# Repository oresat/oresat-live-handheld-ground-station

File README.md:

# Introduction
The OreSat Live Handheld Ground Station (HGS) project provides everything you need to build your own ground station capable of receiving images transmitted from OreSat in Low Earth Orbit.  HGS is designed to be inexpensive, easy to assemble, and simple to use so that it can be built by Middle and High School students.  The entire design is open source to encourage reuse and experimentation.

HGS is a portable unit built around a high gain directional antenna. Using a mobile phone application to locate OreSat, you aim the antenna to get the best possible signal. The live images are then received by the groundstation, error corrections are applied and the image is made available to any WiFi capable device through a built-in web page.

OreSat HGS act as a wifi access point providing an unsecured wireless network named "OreSatLive".  Devices identify the network as a hotspot requiring the user to sign-in for Internet access.  To view the image stream simply:
1. Connect your wifi to the "OreSatLive" network
2. Choose to sign-in when prompted
3. The OreSat Live web interface will open automatically

HGS was created for use with the OreSat mission, but it is designed to be used by any group interested in long range image transmission.  The handheld ground stations can be reused for other cubesat or balloon launches.

Once the final design is completed, users will be able to purchase all of the required parts as a kit from https://www.crowdsupply.com/

# HGS Parts List
All of the required parts to build HGS can be found in the Bill of Materials [(BOM)](BOM.md)

# Hardware Setup
Build your Handheld Ground Station kit according to the [Assembly Instructions](hgs-model/assembly-instructions/OreSat_Live_HGS_Assembly.pdf)

# Software Setup
1. [Download the SD card image oresat_hgs_14_jun_2019.img](https://drive.google.com/a/pdx.edu/uc?id=1BvP8ltkEwoBRSbCfQXceEiuxpVhkSf37&export=download)
2. Write the SD card image to a 2GB or larger card.  The [Raspberry Pi documentation](https://www.raspberrypi.org/documentation/installation/installing-images/) explains the procedure.

# Startup Procedure
1. Install the SD card in Raspberry Pi
2. Insert phone into the holder
3. Connect Raspberry Pi power cable to the USB power bank
4. Load Satellite AR app on phone and select OreSat
5. Point the ground station in the direction of OreSat
3. Connect your viewing devices to the "OreSatLive" wifi network

# Design Details
## Software Design
If you would like to build the software system from source follow the [Build Instructions](software/BUILD.md)

## Mechanical Design
You can 3D print all of the [mechanical parts](hgs-model/README.md)  

## Circuit Board Design
The integrated antenna backplane and matching network [circuit board design files](backplane/README.md)

# Related Projects
[OreSat Live](https://github.com/oresat/oresat-dxwifi-software) for software and firmware used on OreSat satellite

[Mini OreSat](https://github.com/oresat/oresat-live-mini-oresat) combines the OreSat Live software with a Raspberry Pi Zero W + Pi Camera to create platform for hobbyist and classroom experiments with high-altitude ballooning.

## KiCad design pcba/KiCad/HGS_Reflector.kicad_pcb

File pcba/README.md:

# Backplane for Handheld Ground Station
Schematic files for the backplane, including impedence matching circuit for connecting the antenna to the rest of the components.

Schematic files created using KiCad 5.1.2.
- **.pro** to open up Kicad project
- **.kicad_pcb** for the PCB layout
- **.kicad_mod** for the individual footprints

## Microstrip Dimensions
Backplane material: FR-4 PCB material, 0.5 oz copper, 1.58 mm thick, Er 4.34 @ 1 GHz
Note: Do not remove any of the copper ground plane on the other side of the board beneath the traces.  

Microstrip widths for various impedances:
```
50 ohm
	Width:  3.05184 mm
	Length: Arbitrary

83 ohm?
	Width: 1.20938 mm
	Length: Arbitrary

140 ohm
	Width:  0.238155 mm
	Length: Arbitrary
```

## 1/4 Wave Matching Transformer Design:
	Start at connector
	Arbitrary length of 50 ohm
	Lambda/4 length (17.7623 mm) of 83.66 ohm
	Arbitrary length of 140 ohm
	End at the helix element

## Other notes
[Source for Raspberry Pi Zero footprint dimensions](http://www.electronics-lab.com/raspberry-pi-zero-footprint-and-dimensions/)\
[Source for wf-np9202 footprint dimensions](https://www.aliexpress.com/item/wireless-net-card-LAN-NIC-module-AR9271-150M-wireless-LAN-net-card-industrial-module/32746090657.html?tt=sns_none&aff_platform=default&cpt=1557507604073&sk=cC0ydLx2&aff_trace_key=5d988d9ac55b4f4d80da408161a19463-1557507604073-02869-cC0ydLx2&terminal_id=523d634d52754e72ad5634ec5f8829c2)

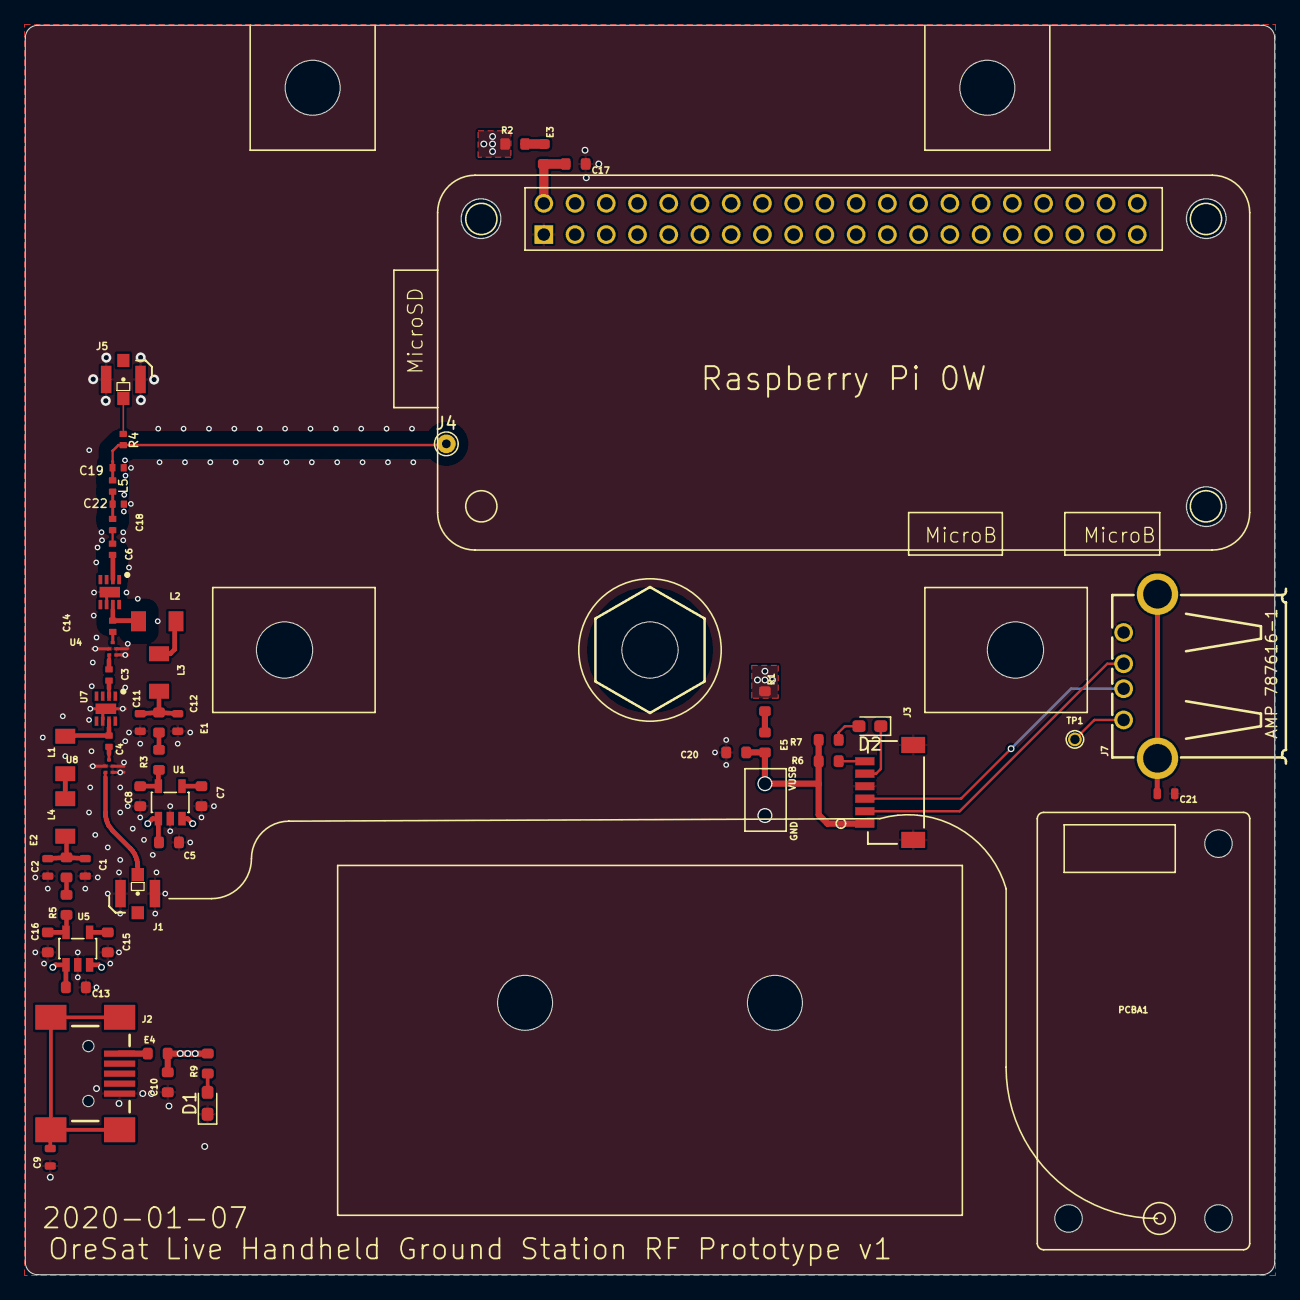
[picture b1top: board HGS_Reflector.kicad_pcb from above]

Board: 4 copper layers, 100.0 x 100.0 mm, 64 parts (0 on the bottom side), 38 nets.

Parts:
@HOLE0, @HOLE1, @HOLE2, @HOLE3, @HOLE4, @HOLE5, @HOLE6: (no value)
C1, C9, C11, C21: 100 pF; 0603-C-NOSILK
C2, C12: 1 uF; 0603-C-NOSILK
C3, C4, C6, C14, C18: 100 pF; 0402-C-NOSILK
C5, C10, C13, C17, C20: 1 uF; 0603-B-NOSILK
C7, C15: 10 nF; 0603-B-NOSILK
C8, C16: 2.2 uF; 0603-B-NOSILK
C19: 0.9 pF; 0402-C-NOSILK
C22: 1.0 pF; 0402-C-NOSILK
D1, D2: Green; LED_0603_1608Metric_Pad1.05x0.95mm_HandSolder
E1, E2, E5: BLM18GG471SZ1D; 0603-B-NOSILK
E3, E4: BLM18DN381SZ1D; 0603-B-NOSILK
J1: U.FL
J2: USB_C_Plug_USB2.0; USB-MINIB
J3: SM06B-SRSS-TB(LF)(SN); CONN_SM06B-SRSS-TB_JST
J4: Conn_01x01_Pin; TestPoint_THTPad_D1.5mm_Drill0.7mm
J5: 132134-10; U.FL
J7: USB_HOST_W/CHASSIS_GND; GHI2_USB_HOST_HORIZONTAL_W_CHASSIS_GND
L1, L2: 10n; L3216C
L3, L4: 8n; L3216C
L5: 4.3 nH; 0402-C-NOSILK
PCBA1: WF-NP9202WF; WF-NP9202
PCBA2: RASP_PI_0WPI_0W; RASP_PI_0W
R1, R2, R3, R5, R6: 0; 0603-B-NOSILK
R4: R_Small_US; 0402-C-NOSILK
R7, R9: 1k; 0603-B-NOSILK
TP1: Test-Point; TestPoint-0.75mm-th
U1, U5: LP2985-N; SOT-23 LP2985
U2, U7: TQP3M9037
U4: QPQ1907
U8: B39162B9417K610; QPQ1907

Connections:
/RF1: C19.2, J4.1, L5.1, R4.2
/RF2: C18.2, C22.1, L5.2
/RF3: C6.2, U2.2 (RF_IN)
/RF4: C14.1, L2.1, U2.7 (RF_OUT)
GND: C1.2, C2.2, C5.1, C7.2, C8.2, C9.1, C10.1, C11.2, C12.2, C13.1, C15.2, C16.2, C17.1, C19.1, C20.1, C21.1, C22.2, D1.1 (K), J1.1 (GND@0), J1.2 (GND@1), J2.A1 (GND), J3.4, J3.7, J3.8 (7), J5.1 (GND@0), J5.2 (GND@1), J7.4 (GND), PCBA2.GND, U1.2 (GND), U2.6 (SHUT_DOWN), U2.9 (GND), U4.2 (GND), U4.3 (GND), U4.5 (GND), U5.2 (GND), U7.6 (SHUT_DOWN), U7.9 (GND), U8.2 (GND), U8.3 (GND), U8.5 (GND)
unnamed: C1.1, C2.1, E2.2, L4.2
unnamed: C11.1, C12.1, E1.2, L3.2
unnamed: C17.2, E3.2, PCBA2.5V
unnamed: C6.1, C18.1
unnamed: C20.2, E5.2, J3.1, R6.1, R7.2
unnamed: D1.2 (A), R9.1
unnamed: D2.2 (A), R7.1
unnamed: D2.1 (K), J3.5
unnamed: E1.1, R3.2
unnamed: E2.1, R5.2
unnamed: E3.1, R2.2
unnamed: E4.1, J2.A4 (VBUS)
unnamed: E5.1, R1.2
unnamed: J1.FEED (SIGNAL), U8.4 (OUT)
unnamed: C9.2, J2.S1 (SHIELD)
unnamed: J3.6, R6.2
unnamed: J5.FEED (SIGNAL), R4.1
unnamed: C21.2, J7.5 (CG1), J7.6 (CG2)
unnamed: J3.2, J7.3 (D+)
unnamed: J3.3, J7.2 (D-)
unnamed: J7.1 (VBUS), TP1.1
unnamed: L1.2, L4.1
unnamed: L2.2, L3.1
unnamed: C7.1, U1.4 (BYPASS)
unnamed: C8.1, R3.1, U1.5 (VOUT)
unnamed: C14.2, U4.1 (IN)
unnamed: C3.1, U4.4 (OUT)
unnamed: C15.1, U5.4 (BYPASS)
unnamed: C16.1, R5.1, U5.5 (VOUT)
unnamed: C3.2, U7.2 (RF_IN)
unnamed: C4.1, L1.1, U7.7 (RF_OUT)
unnamed: C4.2, U8.1 (IN)
VBUS: C5.2, C10.2, C13.2, E4.2, R1.1, R2.1, R9.2, U1.1 (VIN), U1.3 (EN), U5.1 (VIN), U5.3 (EN)

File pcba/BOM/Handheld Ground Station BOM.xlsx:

Count | Ref Des | Value | MFR | MPN | Description | Size | Generic? | Digi-Key Part No. | Mouser Part No. | Mini-Circuits Link
4 | C1, C11, C9, C21 | 100 pF | Murata | GCM1885C1H101JA16D | CAP CER 100PF 50V C0G/NP0 0603 | 0603 | Y | 490-4767-1-ND
7 | C2, C5, C10, C12, C13, C17, C20 | 1 uF | Yageo | CC0603KRX5R7BB105 | CAP CER 1UF 16V X5R 0603 | 0603 | Y | 311-1444-1-ND
6 | C3, C4, C6, C14, C18, C19 | 100 pF | Murata | GCM1555C1H101JA16D | CAP CER 100PF 50V C0G/NP0 0402 | 0402 | Y | 490-10669-1-ND
2 | C7, C15 | 10 nF | Murata | GCD188R71H103KA01D | CAP CER 10000PF 50V X7R 0603 | 0603 | Y | 490-17738-1-ND
2 | C8, C16 | 2.2 uF | Murata | GRM188R61E225KA12D | CAP CER 2.2UF 25V X5R 0603 | 0603 | Y | 490-10731-1-ND
3 | E1, E2, E5 | BLM18GG471SZ1D | Murata | BLM18GG471SZ1D | FERRITE BEAD 470 OHM 0603 1LN | 0603 | Y | 490-16658-1-ND
2 | E3, E4 | BLM18DN381SZ1D | Murata | BLM18DN381SZ1D | FERRITEBEAD SMD Z100MHZ=380OHM 8 | 0603 | Y | 490-18574-1-ND
1 | J1 | U.FL | TE Connectivity | 1909763-1 | CONN UMCC JACK STR 50OHM SMD |  | Y | A118077CT-ND
1 | J2 | USB_MINI-B_SMT | SparkFun | PRT-00587 | USB Mini-B SMD Connector |  | Y |  | 474-PRT-00587
1 | J3 | SM06B-SRSS-TB(LF)(SN) | JST Sales America Inc. | SM06B-SRSS-TB(LF)(SN) | CONN HEADER SMD R/A 6POS 1MM |  | Y | 455-1806-1-ND
2 | J5, J6 | 132134-10 | Amphenol RF | 132134-10 | CONN SMA JACK STR 50 OHM SMD |  | Y | ARF2755-ND
1 | J7 |  | SparkFun | PRT-09011 | USB Female Type A SMD Connector |  | Y |  | 474-PRT-09011
2 | L1, L2 | 10nH | Pulse Electronics Network | PE-1206CD100JTT | FIXED IND 10NH 1A 80 MOHM SMD | L3216C | Y | 1840-1138-1-ND
2 | L3, L4 | 8nH | Murata | LQW31HN8N8J03L | Fixed Inductors 1206 8.8nH +/-5% | L3216C | Y |  | 81-LQW31HN8N8J03L
2 | LED1, LED2 | GREEN | Rohm Semiconductor | SML-E12M8WT86 | LED GREEN DIFFUSED 0603 SMD | 0603 | Y | 511-1584-1-ND
1 | PCBA1 | WF-NP9202WF | Aliexpress | WF-NP9202WF | AR9721 based WiFi transciever |  | N
1 | PCBA2 | RASP_PI_0W | Raspberry Pi | RASP_PI_0WPI_0W | Raspberry Pi Zero W |  | N
5 | R1, R2, R3, R5, R6 | 0 | Yageo | RC0603JR-070RL | RES SMD 0 OHM JUMPER 1/10W 0603 | 0603 | Y | 311-0.0GRCT-ND
1 | R4 | 150 | Panasonic Electronic Components | ERJ-2RKF1500X | RES SMD 150 OHM 1% 1/10W 0402 | 0402 | Y | P150LCT-ND
2 | R7, R9 | 1k | Yageo | RC0603FR-071KL | RES SMD 1K OHM 1% 1/10W 0603 | 0603 | Y | 311-1.00KHRCT-ND
2 | U1, U2 | LP2985XX-N | TI | LP2985IM5X-3.3/NOPB | IC REG LINEAR 3.3V 150MA SOT23-5 |  | N | LP2985IM5X-3.3/NOPBCT-ND
1 | U3 | NCS3-272+ | Mini-Circuits | NCS3-272+ | 1:3 LTCC Transformer, 2250 - 2725 MHz, 50Ω |  | N |  |  | https://www.minicircuits.com/WebStore/dashboard.html?model=N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
2 | U4, U5 | QPQ1907 | Qorvo | QPQ1907SR | Signal Conditioning Coexist BAW FILTER |  | N |  | 772-QPQ1907SR
2 | U6, U7 | LNA-TQP3M9037 | Qorvo | TQP3M9037 | RF Amplifier 1.5-2.7GHz |  | N |  | 772-TQP3M9037
1 | CABLE1 |  | JST Sales America Inc. | A06SR06SR30K51A | JUMPER 06SR-3S - 06SR-3S 2" |  | N | 455-2999-ND

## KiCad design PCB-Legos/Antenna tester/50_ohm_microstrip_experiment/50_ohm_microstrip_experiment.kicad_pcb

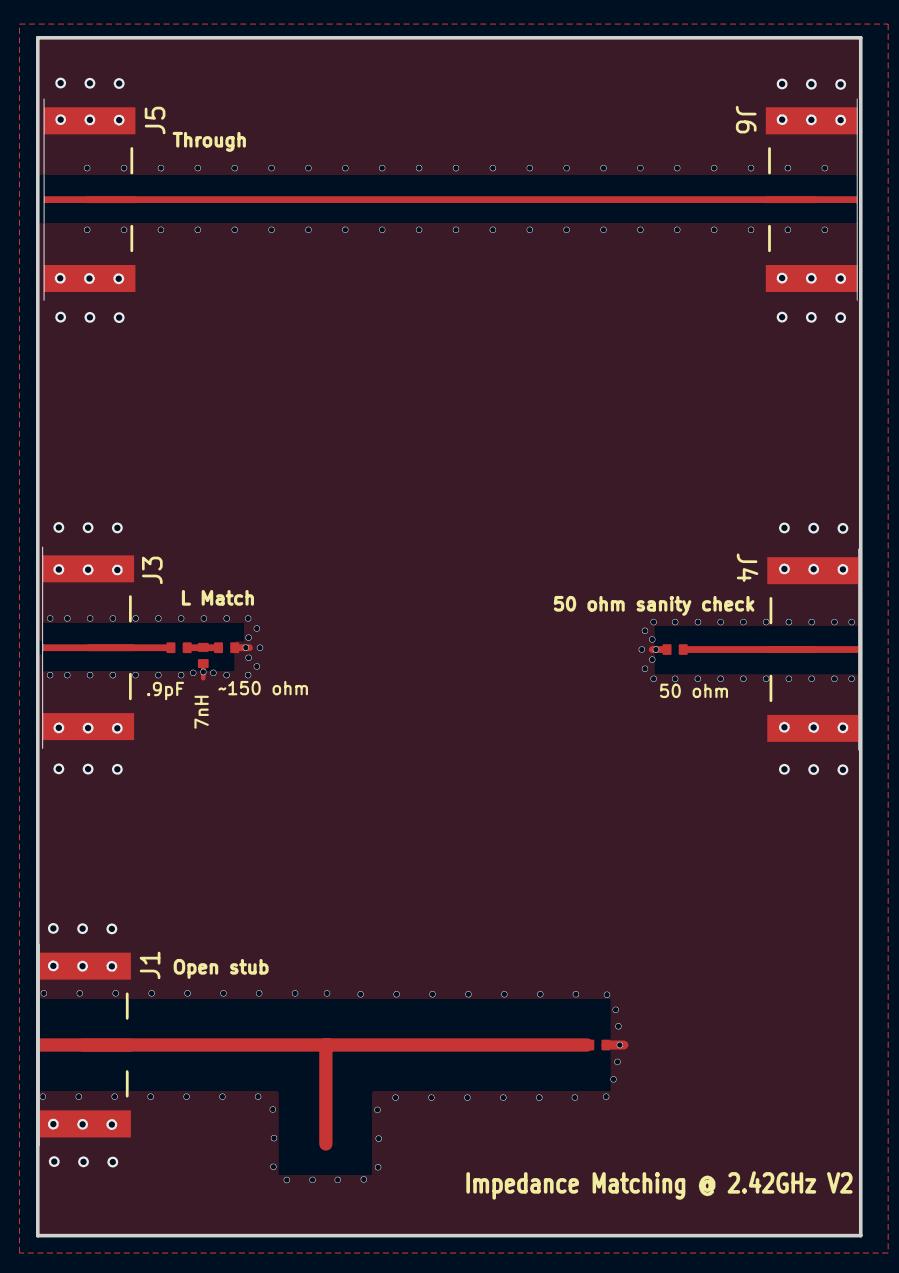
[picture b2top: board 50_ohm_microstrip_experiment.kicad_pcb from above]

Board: 4 copper layers, 45.7 x 66.5 mm, 10 parts (0 on the bottom side), 5 nets.

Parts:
C1: .9pF; .0402-C-NOSILK
J1, J3, J4, J5, J6: Conn_Coaxial; CONN_142-0701-851_CIN
L1: 7nH; .0402-C-NOSILK
R1: 50; .0402-C-NOSILK
R5: ~150 ohm; .0402-C-NOSILK
R6: 50 ohm; .0402-C-NOSILK

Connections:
GND: J1.2 (Ext), J1.3, J1.4, J1.5, J3.2 (Ext), J3.3, J3.4, J3.5, J4.2 (Ext), J4.3, J4.4, J4.5, J5.2 (Ext), J5.3, J5.4, J6.2 (Ext), J6.3, J6.5, L1.2, R1.1, R5.1, R6.1
unnamed: J1.1 (In), R1.2
unnamed: C1.2, J3.1 (In), J4.1 (In)
unnamed: J5.1 (In), J6.1 (In)
unnamed: C1.1, L1.1, R5.2, R6.2

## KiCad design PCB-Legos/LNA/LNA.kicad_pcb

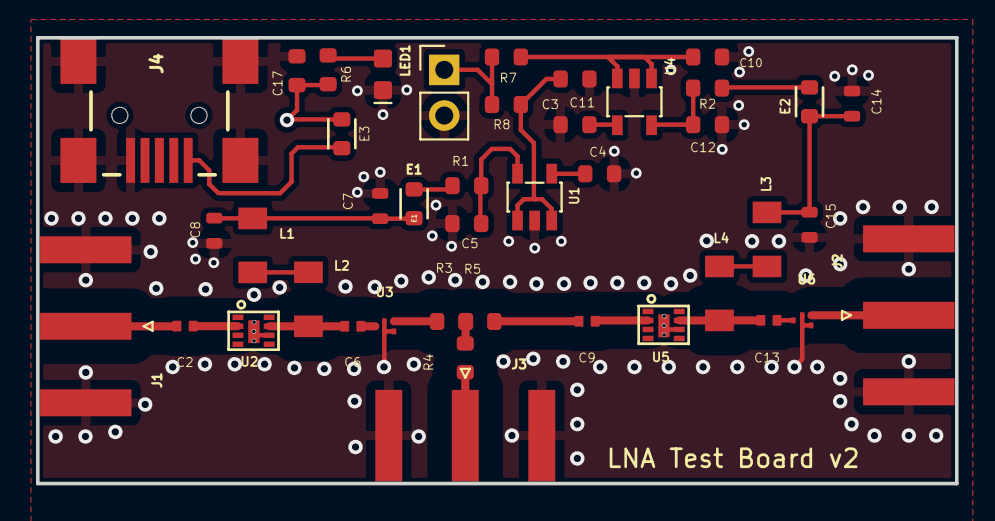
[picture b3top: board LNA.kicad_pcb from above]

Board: 4 copper layers, 51.1 x 24.8 mm, 42 parts (0 on the bottom side), 26 nets.

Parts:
C2, C6, C9, C13: 100 pF; .0402-C-NOSILK
C3, C10, C17: 1 uF; .0603-B-NOSILK
C4, C11: 10 nF; .0603-B-NOSILK
C5, C12: 2.2 uF; .0603-B-NOSILK
C7, C14: 100 pF; .0603-C-NOSILK
C8, C15: 1 uF; .0603-C-NOSILK
E1, E2: BLM18GG471SZ1D; .0603-B
E3: BLM18DN381SZ1D; .0603-B
H2: VUSB; PinHeader_1x02_P2.54mm_Vertical
J1, J2, J3: Conn_Coaxial; SMA_Amphenol_132289_EdgeMount
J4: 474-PRT-00587; USB-MINIB
L1, L3: 8 nH; L3216C
L2, L4: 10 nH; L3216C
LED1: GREEN; LED-0603
R1, R2, R3, R4, R5, R7, R8: 0; .0603-B-NOSILK
R6: 1k; .0603-B-NOSILK
U1, U4: LP2985XX-N; SOT-23
U2, U5: LNA-TP3M9037; TP3M9037
U3, U6: QPQ1907

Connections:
GND: C3.1, C4.2, C5.2, C7.2, C8.2, C10.1, C11.2, C12.2, C14.2, C15.2, C17.1, H2.2, J1.2 (Ext), J2.2 (Ext), J3.2 (Ext), J4.GND, J4.S1 (SHIELD), J4.S2 (SHIELD), J4.S3 (SHIELD), J4.S4 (SHIELD), LED1.C, U1.2 (GND), U3.GND, U3.GND2 (GND), U3.GND3 (GND), U4.2 (GND), U6.GND, U6.GND2 (GND), U6.GND3 (GND)
unnamed: C2.1, J1.1 (In)
unnamed: C3.2, R8.1, U1.1 (VIN), U1.3 (EN)
unnamed: C4.1, U1.4 (BYPASS)
unnamed: C5.1, R1.1, U1.5 (VOUT)
unnamed: C6.1, L2.1
unnamed: C6.2, U3.INPUT (RF_IN)
unnamed: C7.1, C8.1, E1.2, L1.2
unnamed: C9.1, R5.2
unnamed: C10.2, R7.1, U4.1 (VIN), U4.3 (EN)
unnamed: C11.1, U4.4 (BYPASS)
unnamed: C12.1, R2.1, U4.5 (VOUT)
unnamed: C13.1, L4.1
unnamed: C13.2, U6.INPUT (RF_IN)
unnamed: C14.1, C15.1, E2.2, L3.2
unnamed: E1.1, R1.2
unnamed: E2.1, R2.2
unnamed: E3.1, J4.VBUS
unnamed: J2.1 (In), U6.OUTPUT (RF-OUT)
unnamed: J3.1 (In), R4.2
unnamed: L1.1, L2.2
unnamed: L3.1, L4.2
unnamed: LED1.A, R6.1
unnamed: R3.1, U3.OUTPUT (RF-OUT)
unnamed: R3.2, R4.1, R5.1
VUSB: C17.2, E3.2, H2.1, R6.2, R7.2, R8.2

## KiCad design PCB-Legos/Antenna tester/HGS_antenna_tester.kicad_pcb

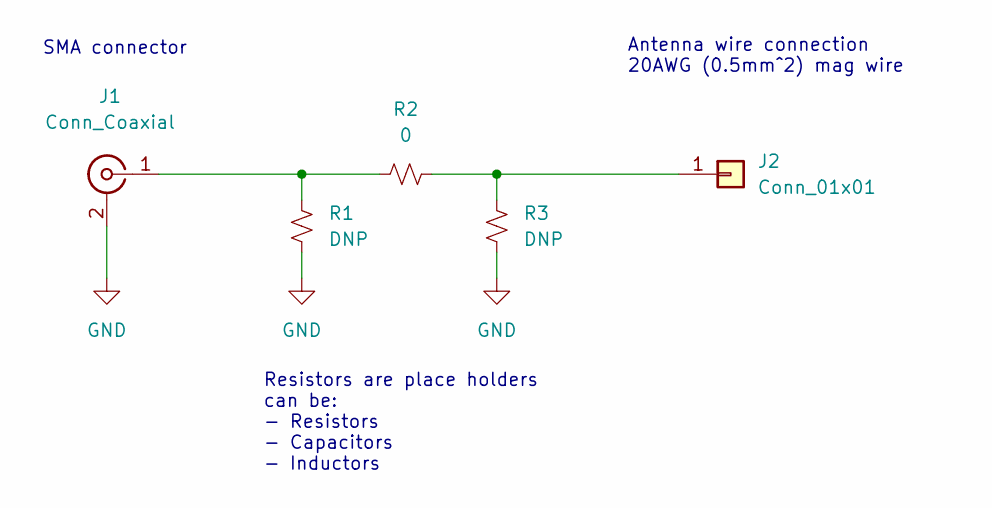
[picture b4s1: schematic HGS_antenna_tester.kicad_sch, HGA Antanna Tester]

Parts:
J1: Conn_Coaxial; SMA_Amphenol_132134-10_Vertical
J2: Conn_01x01; SolderWire-0.5sqmm_1x01_D0.9mm_OD2.1mm
R1, R3: DNP; R_0402_1005Metric_Pad0.72x0.64mm_HandSolder
R2: 0; R_0402_1005Metric_Pad0.72x0.64mm_HandSolder

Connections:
GND: J1.2 (Ext), R1.2, R3.2
unnamed: J1.1 (In), R1.1, R2.1
unnamed: J2.1, R2.2, R3.1

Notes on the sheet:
Antenna wire connection 20AWG (0.5mm^2) mag wire
SMA connector
Resistors are place holders can be: - Resistors - Capacitors - Inductors

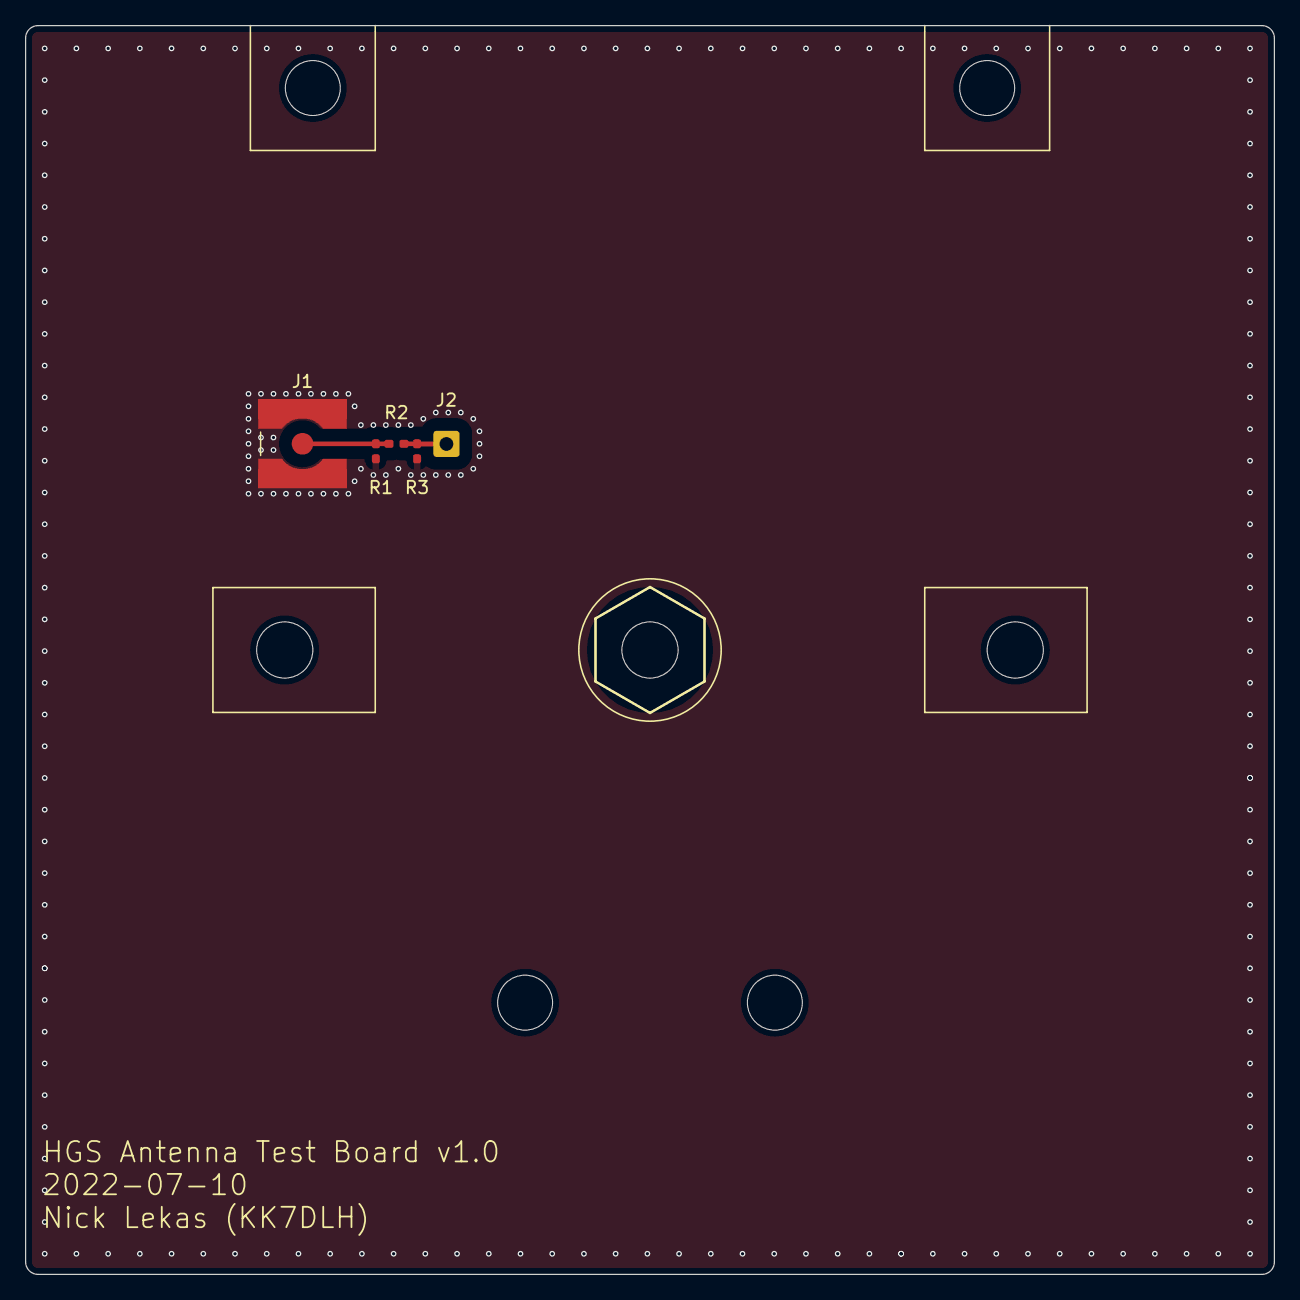
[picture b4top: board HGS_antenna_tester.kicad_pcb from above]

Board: 4 copper layers, 100.0 x 100.0 mm, 12 parts (0 on the bottom side), 3 nets.

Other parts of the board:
@HOLE0, @HOLE1, @HOLE2, @HOLE3, @HOLE4, @HOLE5, @HOLE6: (no value)

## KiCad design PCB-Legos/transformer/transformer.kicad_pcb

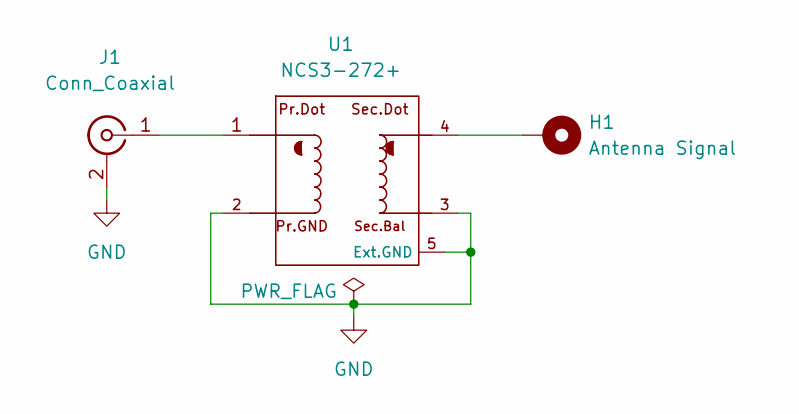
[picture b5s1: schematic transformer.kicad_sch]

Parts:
H1: Antenna Signal; Pin_D0.7mm_L6.5mm_W1.8mm_FlatFork
J1: Conn_Coaxial; J-Amphenol-132134-10-SMA-F-SMT-vertical
U1: NCS3-272+; U-Minicircuits-GE0805C-9

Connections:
GND: J1.2 (Ext), U1.2, U1.3, U1.5 (Ext.GND)
unnamed: H1.1, U1.4
unnamed: J1.1 (In), U1.1

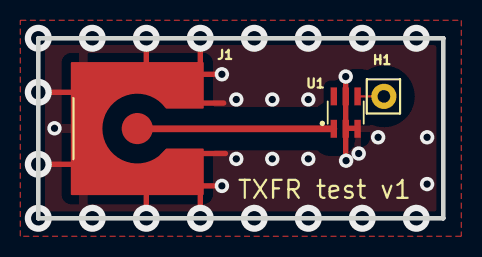
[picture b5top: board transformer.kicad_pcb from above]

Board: 4 copper layers, 22.5 x 10.0 mm, 3 parts (0 on the bottom side), 3 nets.

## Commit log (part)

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2019-02-11 Added antenna segment 3d print files.
    Added the SLDPRT and STL files of the helical antenna (initial version). Also added initial version of README files for the associated folders.
2019-02-11 Improved helical antenna 3d model to disallow incorrect assembly
    Converted a peg to a 'key' peg to disallow incorrect rotation.
2019-02-26 Reorganized 3d model folders, changed antenna pegs to square.
    Reorganized 3D models into one folder, with added documentation, to support a mockup assembly.
    Replaced previous three round pegs with a single square peg with an alignment peg attached to one side. Should allow for a single top cap that can be attached in four orientations for the 4 antenna a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
2019-03-26 Uploaded ap mode setup script for raspberry pi
2019-04-14 Added basic simple HTML page for livestream
2019-04-14 Changed body text color to contrast background
2019-04-14 Changed color of overlay text to green
2019-04-19 Added latest streaming method with pause button
2019-04-24 Removed tabs and adjusted holes for #4 screws
2019-04-24 Started KiCad project for backplane
2019-04-27 Handle model: smoothed edges, added 1/4-20 nut slot for mounting, etc.
    Added screw insets for the clamp.
    Added exported model for printing.
2019-04-27 Antenna_endcap: changed name to "Antenna_Base_Clamp", etc
    Made clamp tighter (to size of peg without extra clearance.)
    Added .stl for printing.
2019-04-27 Added fastener dimensions to documentation. Edited handle to match.
2019-04-27 Phone_Clamp_base: Moved holes in, extended slots, clamp: Moved holes in
2019-04-29 Made most of the backplane design, no idea if it'll actually work
    Missing impedance matching bit
2019-04-29 Added new display section for useful times
    Local time is no longer over streaming images.
2019-04-29 Moved javascript to separate files to clean HTML
2019-04-29 Cleaned up method for blinking colons for times
2019-04-29 Added placeholder altitude
    Also some minor change to displaying values for the table with
    AOS and LOS.
2019-04-30 Fixed reference to footprint library location
2019-05-01 Adjusted backplane layout
2019-05-01 Added gerber files to use with router
2019-05-01 Updated footprint and PCB layout
    Accidently undid a new through-hole in last commit.
    Updated footprint for microstrip to include clearance.
2019-05-08 Updated microstrip and moved components around
    Microstrip now has solder mask on the tips for soldering wires to it,
    and holes nearby for connecting coax cable and antenna.
    RPi and WiFi module mount holes have been moved to match first prototype
    assembled for open house.
2019-05-09 Updated silkscreen and REF values for footprints
    Footprints now have unique names for easy reference in library.
    Names for footprints have been moved around so that they don't overlap
    on PCB layout.
    Labels for RPi Zero connections moved outside box for visibility when
    RPi is mounted onto backplane.
2019-05-09 Added version number in silkscreen
2019-05-09 Updated Phone holder base to 3.2mm holes and slots
2019-05-09 Updated handle clamp to 3.2mm holes
2019-05-09 Added OreSat logo to silkscreen
    Included dxf version of logo needed to import to Kicad
    Added logo as footprint (includes version number)
2019-05-10 Updated footprint for Raspberry Pi Zero
2019-05-13 Added holes for strings and modified microstrip
    Board layout now reflects what users see when using the product from the
    back of the board. The side of the microstrip where the antenna will feed
    in now has a rectangular hole.
2019-05-13 Added ground planes and vias
2019-05-16 Antenna base clamp: made slightly thicker
2019-05-16 Handle: suppressed features, shortened handle (reverting to no battery)
    Suppressed USB slot
    Suppressed battery compartment
    Shortened handle back to previous length for more solid assembly
    Made bolt holes slightly larger
    Chamfered bolt head insets for printing
    Filleted handle top corners
2019-05-16 Phone holder base: Chamfered bolt head insets, Enlarged bolt holes
2019-05-16 Helical antenna segment: enlarged wire attachment loop
2019-05-25 Adding major changes to transformer and others
    Moved Atheros module out from under phone clamp for easier assembly.
    Slot for antenna wire to feed through is now a edge cut.
    Through-hole to GND plane on opposite end of transformer is now a SMD for
    a UFL connector.
    Transformer clearance is now a copper trace isolating the microstrip.
2019-05-26 Changed antenna feed slot width to be 1.5mm and other
    Cleaned up floating unnecessary silkscreen
    Removed solder mask for mounting holes
    Updated version number text for HGS
2019-05-28 Updated standard to M3.5/#6 bolts
2019-05-28 Handle/split handle: updated fastener sizes to new standard
    Also enlarged standard sizes slightly
2019-05-28 Readme: changed standard to next size of bolt up, M3.5 to M4
    Hopefully easier to find.
2019-05-28 Handle_Clamp: Updated to M4
2019-05-28 Added new model phone and battery holder bottom section
2019-05-28 Added base section of new Phone and battery holder design
2019-05-29 Replaced transformer isolation with "Keep Out" zones
    Was previously using a copper trace to isolate the transformer to prevent
    copper fill to get around it. Found keep out zone option to define areas
    that we don't want copper to be in.
2019-06-02 Adding major final changes for transformer strip
    Moved transformer parts closer to antenna by 1mm
    Transformer microstrip reverted to original intended size
    Added footprint for 0402 capacitor to replace gap between U.FL and strip
    Modified U.FL footprint pads to be "solid" to allow for copper fill to
    connect to the GND pads
    Phone Clamp and Handle mount holes changed to 4.5mm
2019-06-02 Phone&Battery_Holder_Base: moved holes out to the sides and longer legs
    Also thinner body
2019-06-02 Handle: Increased clamp base thickness to match phone&battery holder
2019-06-02 Phone&Battery_Holder: Lots of changes to fit together better&new battery
    Bottom: added slot for Top and extended battery section for new battery spec
    Top: Lengthened base to fit along Bottom for much larger range of phone sizes
2019-06-02 Antenna_Base_Clamp: added roof and bolt hole and inset
2019-06-02 Antenna_Cap: Added bolt hole and hex inset
2019-06-06 Changed velocity units to metric
    Was mph. Is now km/h
2019-06-13 Updated README formatting for markdown
2019-06-13 Added section titles to backplane README
    Also added descriptions of important Kicad files
2019-06-20 Restructure files and improve documentation
2019-06-21 Added assembly instructions PDF and source Latex
    README link has been linked to go straight PDF
2019-06-21 Removed Kicad temp and unecessary files
    Added gitignore to prevent pushes of temp files
2019-07-16 updated antenna segments
2019-07-17 asjkdfnajks
2019-07-19 updated antenna stuff
2019-07-24 updated antenna, added build folder for STLs
2019-07-26 updated hgs assembly
2019-08-12 updated CAD assembly and added screenshots
2019-08-12 started translating board files from heathenous Kicad to gloroius eagle
2019-08-13 updated bill of materials
2019-08-13 handheld ground station eagle mockup
2019-08-13 updated hgs mockup
2019-08-15 updated rubber band holding parts and their STLs
2019-08-20 "auto-generated from update_repos.py"
2019-12-05 updated battery holder for velcro location. updated groundplane with keepout locations and dxf
2020-01-08 added STLs of the current CAD
2020-04-17 Archived kicad files, added right design rules to EAGLE files.
2020-05-07 updated HGS exploded view
2020-05-12 Small reorganization, it's reflector not backplane. Updated DXF layer for latest MCAD. After discussion, decided to move LNA and all sensitive parts to the top of the board which is now the helical s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
2020-07-13 Updated handheld. Increased number of segments, extended rod.
2020-07-19 removed temp files
2020-08-02 Completed schematic with respect to the current block diagram
2020-08-02 Fixed USB pin issue
2020-08-16 Schematic, board and BOM updates
2020-08-18 Correcting the file name for the BOM
2020-08-20 I've completed the BOM for version 1 of the PCB for the reflector. Regarding the board and schematic themselves, the board needs to be mapped out with all parts oriented before being reviewed.
2020-10-06 Fixed a bad cut.
2020-10-18 I completed the physical layout of the board for HGS. Currently, I just need to sort through some DRC errors that I don't know how to fix, and do a design review.
2020-11-15 I incorporated the 1/4 wave transformer part (TM-QWT-2.422GHz.lbr) into the HGS reflector board, but I have not yet consulted with the person who designed the part in order to situate it properly.
2020-11-22 I continued optimizing the trace lengths for the parts on the HGS board, but have not yet been able to situation the 1/4 wave transformer part on the ground plane with the other parts.
2020-11-22 Updated CAD to work with new helical dimensions
2020-11-29 Since the team working on HGS decided to switch from a 2 layer board to a 4 layer board, I began laying out the HGS parts on a new board with 4 layers. Currently, I have a number of questions regardi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
2020-12-02 Updated CAD
2020-12-06 Fixed hex trap CAD
2020-12-06 Last Thursday, I updated the HGS board to its actual shape by importing the the DXF file that Marvin Lin sent me. I began work on re-routing the board to fit within the DXF dimensions.
2020-12-12 With the DXF layer properly configured, I positioned all parts onto the board and completed all of the routing. However, there are a few DRC issues involving details of footprints that need to be cha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
2020-12-13 I made sure that all the signals were completely routed, and fixed the clearance issue with the wire going to the center by replacing the center drill hole with a large via that goes directly to the 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
2020-12-22 Fixed tolerance issue with hex trap and various other parts
2020-12-23 I finalized the schematic and routing of the board for HGS. Note that I adjusted the dxf layer by adding a fourth drill hole underneath the atheros card. It is ready for a design review.
2020-12-23 Added antenna side DXF and fixed broken assembly relations
2020-12-25 After connecting the Pi 0W footprint to the ground plane, I fixed the issue of the Pi 0W pin header floating.
2020-12-27 Removed script.
2021-01-04 Update for Oliver's series of RF tests to see if we can really do this HGS thing. Took Nohl's board and cleaned it up a bit; the LNA and PS and other things are just for fun; the real purpose of this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
2021-01-07 Switched edge fired SMA connectors to Oliver's fancy SMT vertical connectors.
2021-01-08 Part and BOM cleanup
2021-01-24 I made a few additions to the HGS BOM before Oliver Jones made a new BOM.
2021-05-24 Modified design for antenna pitch of 28.6mm and diameter of 43mm
2021-11-13 Added depression for new feed system
2022-02-07 NICK!!!!
    Learned that KiCad needs the .wks file
2022-04-18 transformer test board
    test board for 3:1 balun transformer
2022-04-21 Fixed .gitignore for KiCAD 6, removed backups and other temp files, updated board file with 4 layer oshpark from the oresat-kicad repo, moved antenna much closer to the transformer and reduced the tr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
2022-04-21 Added kicad submodule
2022-04-21 Updated .gitignore.
2022-04-21 Sent off for Fab, v1.0
    Updated libraries and library paths; might actually not be terrible now with the submodule? Fixed footprint of transformer and rotated 90 degrees; made board OCD compliant and did via cleanup.
2022-04-21 Updated library paths to be more sane, especially for footprints. Then unmasked the vias along the edges so that we can get castellated edges. Also reduced the size of the antenna hole, no reason to 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
2022-04-22 Added datasheets to symbols, and 3D model of SMA connector to PCB
2022-04-29 LNA Board
    LNA test board with both stages. Has ability to test each stage.
2022-05-01 LNA
    Fixed minor issues in RF path.
2022-05-05 LNA Board
    LNA Test board with ability to test each stage
2022-05-12 LNA Test Board
    PCB to test each stage ofthe HGS LNA
2022-05-23 LNA BOM added
    BOM of LNA test board
2022-07-10 fixed microstrip width and moved SMA away from R1
2022-07-10 pulled away the solder mask from the transmission line
2022-07-10 pulled refdes's away from stiching
2022-10-30 LNA Test Board
    Reviewed work done during capstone. Everything seems ready to build and test.
2023-02-09 50 Ohm microstrip
    Test boards with a through, impedance matching network and 50ohm load test
2023-05-14 Matching Board with open stub
    Added extra vias around pads
2023-05-25 Reduced SMA GND pin thermal relief
    Reduced SMA GND pin thermal relief also noticed a few pads not connected to GND net
2023-05-26 Fixed issues with backside SMA connector GND pins
    backside GND pins had not net. Connected them to GND net
2023-05-26 Better .gitignore file.
2024-09-11 deleted temp files
2024-09-13 fixed reference designators, fixed symbol/footprint pads and pins, added impedance matching at helical
